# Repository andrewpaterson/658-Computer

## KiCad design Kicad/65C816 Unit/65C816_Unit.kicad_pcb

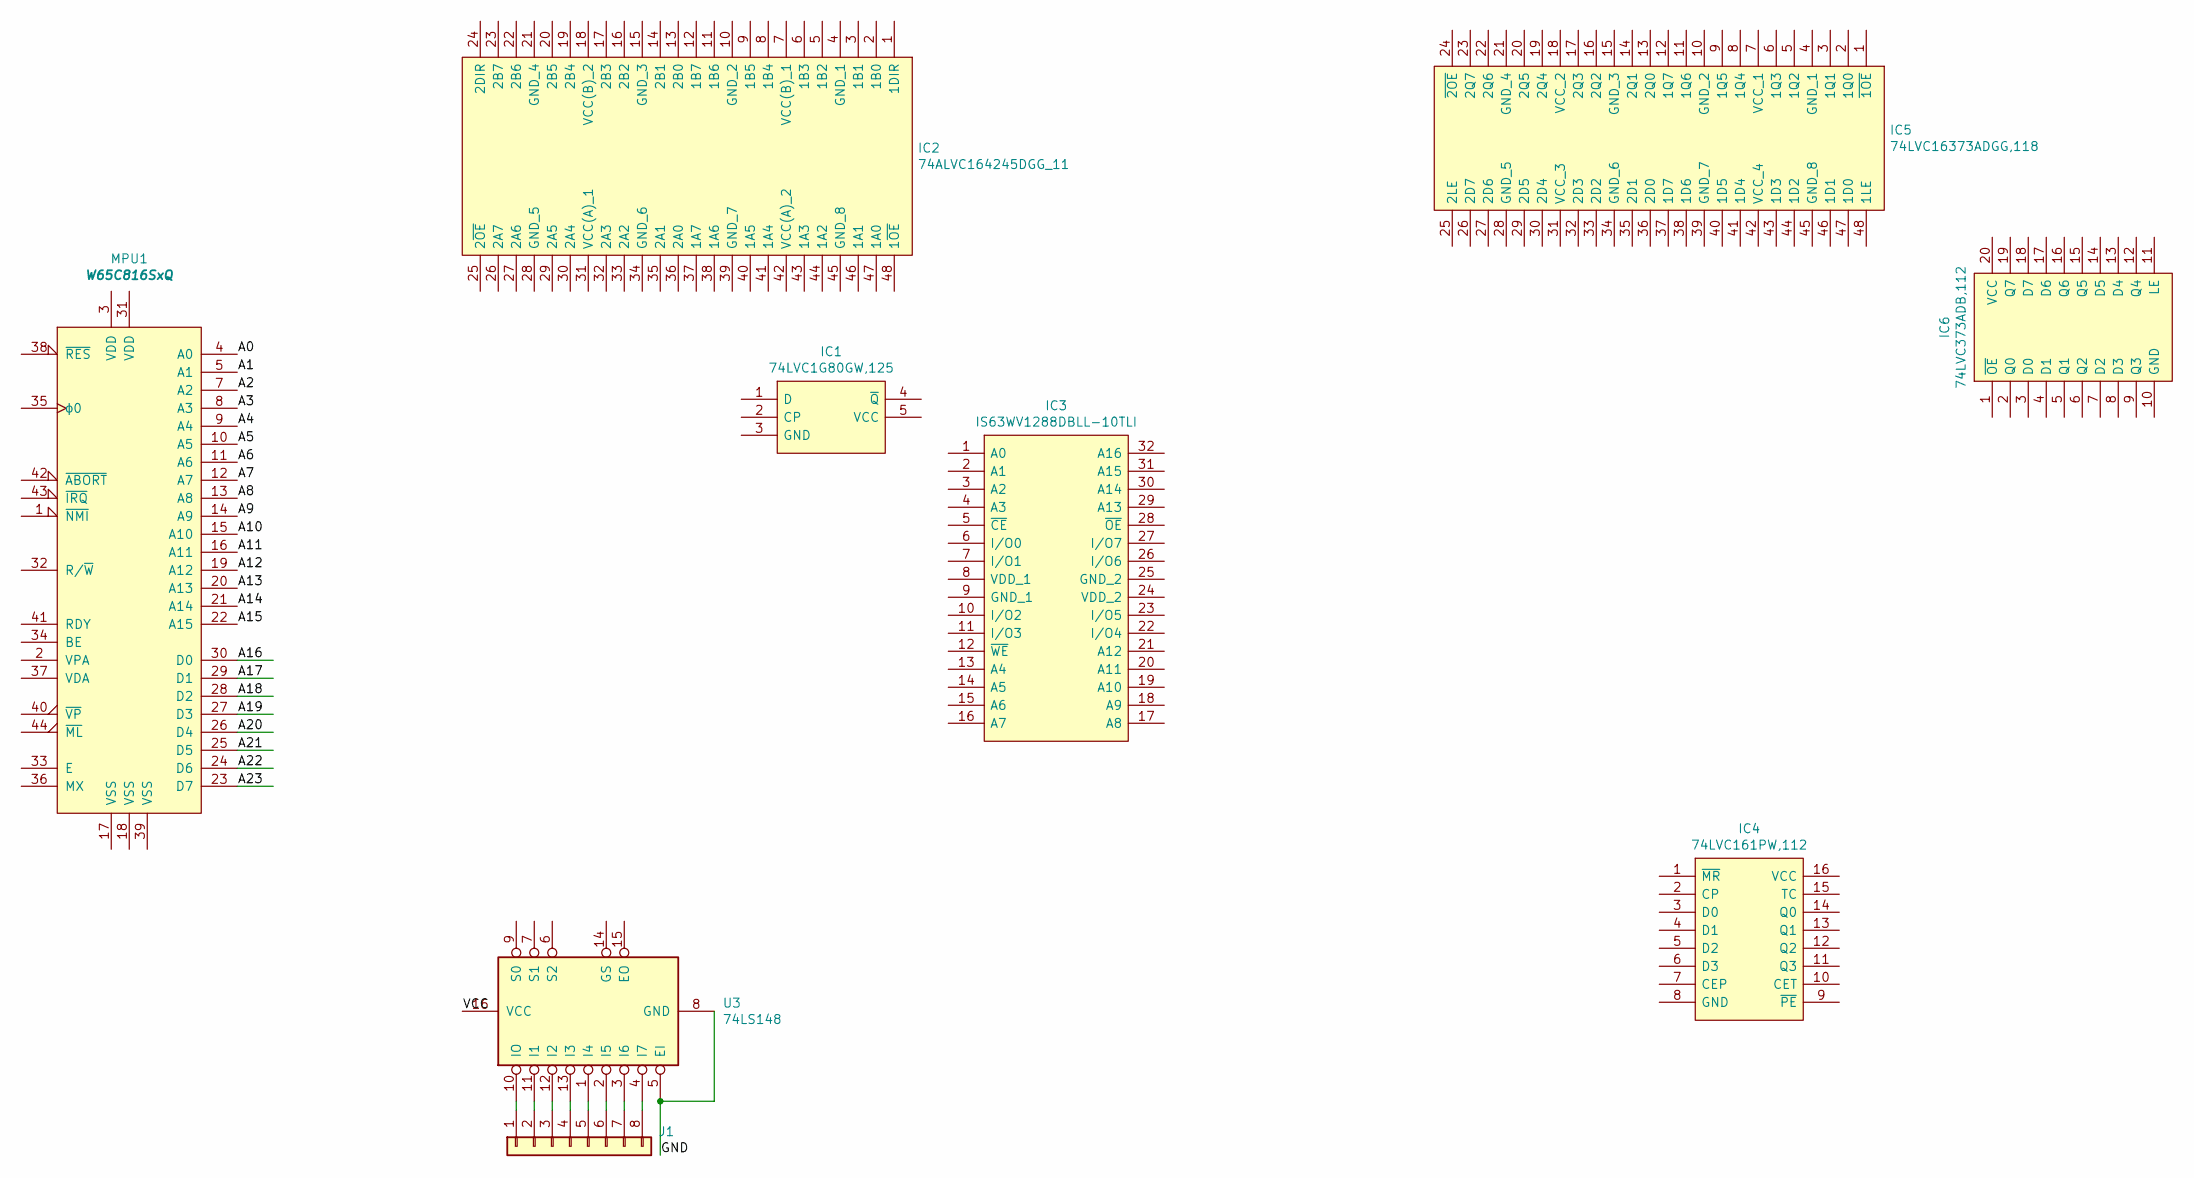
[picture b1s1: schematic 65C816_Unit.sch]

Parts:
IC1: 74LVC1G80GW,125; SOT65P212X110-5N; Mouser Part Number 771-LVC1G80GW125
IC2: 74ALVC164245DGG_11; SOP50P810X120-48N; Mouser Part Number 771-74ALVC164245
IC3: IS63WV1288DBLL-10TLI; SOIC127P1176X120-32N; Mouser Part Number 870-63WV1288DB10TLI
IC4: 74LVC161PW,112; SOP65P640X110-16N; Mouser Part Number 771-LVC161PW112
IC5: 74LVC16373ADGG,118; SOP50P810X120-48N; Mouser Part Number 771-74LVC16373ADGG1
IC6: 74LVC373ADB,112; SOP65P775X200-20N; Manufacturer_Part_Number 74LVC373ADB,112
J1: Conn_01x08; PinHeader_1x08_P2.54mm_Vertical
MPU1: W65C816SxQ; PQFP-44_10x10mm_P0.8mm
U3: 74LS148; SOIC-16_4.55x10.3mm_P1.27mm

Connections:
/A0: MPU1.4 (A0)
/A1: MPU1.5 (A1)
/A2: MPU1.7 (A2)
/A3: MPU1.8 (A3)
/A4: MPU1.9 (A4)
/A5: MPU1.10 (A5)
/A6: MPU1.11 (A6)
/A7: MPU1.12 (A7)
/A8: MPU1.13 (A8)
/A9: MPU1.14 (A9)
/A10: MPU1.15 (A10)
/A11: MPU1.16 (A11)
/A12: MPU1.19 (A12)
/A13: MPU1.20 (A13)
/A14: MPU1.21 (A14)
/A15: MPU1.22 (A15)
/A16: MPU1.30 (D0)
/A17: MPU1.29 (D1)
/A18: MPU1.28 (D2)
/A19: MPU1.27 (D3)
/A20: MPU1.26 (D4)
/A21: MPU1.25 (D5)
/A22: MPU1.24 (D6)
/A23: MPU1.23 (D7)
/GND: U3.5 (EI), U3.8 (GND)
/VCC: U3.16 (VCC)
unnamed: J1.1, U3.10 (IO)
unnamed: J1.2, U3.11 (I1)
unnamed: J1.3, U3.12 (I2)
unnamed: J1.4, U3.13 (I3)
unnamed: J1.5, U3.1 (I4)
unnamed: J1.6, U3.2 (I5)
unnamed: J1.7, U3.3 (I6)
unnamed: J1.8, U3.4 (I7)

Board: 2 copper layers, 9 parts (0 on the bottom side), 9 nets, no tracks yet.

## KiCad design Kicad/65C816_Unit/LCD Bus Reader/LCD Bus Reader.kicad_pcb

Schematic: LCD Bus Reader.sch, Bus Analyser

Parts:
C1, C2, C3: C; C_Disc_D3.8mm_W2.6mm_P2.50mm
D1, D2: D_Zener; D_A-405_P7.62mm_Horizontal
D3, D4, D5, D6: LED; LED_D5.0mm
D7, D8, D9, D10, D11, D12, D13, D14, D15, D16, D17, D18, D19, D20, D21, D22, D23, D24, D25, D26, D27, D28, D29, D30, D31, D32, D33, D34, D35, D36, D37, D38, D39, D40, D41, D42, D43, D44, D45, D46: 1N4148; D_T-1_P5.08mm_Horizontal
J1: Conn_01x02_Male; PinHeader_1x02_P2.54mm_Vertical
J2: Conn_01x24_Male; PinHeader_1x24_P2.54mm_Vertical
J3: Conn_01x03_Male; PinHeader_1x03_P2.54mm_Vertical
J4, J5: Conn_01x08_Male; PinHeader_1x08_P2.54mm_Vertical
R1, R2, R3, R4, R5, R6, R7, R8, R9, R10, R11, R12, R13, R14, R15, R16, R17, R18, R19, R20, R21, R22, R23, R24, R25, R26, R27, R28, R29, R30, R31, R32, R33, R34, R35, R36, R37, R38, R39, R40, R41, R42, R43, R44, R45: R; R_Axial_DIN0204_L3.6mm_D1.6mm_P5.08mm_Horizontal
RV1: R_POT; Potentiometer_Omeg_PC16BU_Vertical
U1: Pico; RPi_Pico_SMD_TH
U2: RC1602A; NMTC-S16205
U3: L7805; TO-220-3_Vertical
U4, U6, U7, U8, U9: 74LS373; SO-20_12.8x7.5mm_P1.27mm
U5: 74LS138; SO-16_3.9x9.9mm_P1.27mm

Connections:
+12V: J1.1, U3.1 (IN)
/0V: D2.1 (K), D3.1 (K), J1.2, RV1.1, U3.2 (GND)
/1.6V: C1.2, C2.2, C3.2, D1.2 (A), D4.1 (K), D5.1 (K), D6.1 (K), R1.2, U1.3 (GND), U1.23 (GND), U1.28 (GND), U1.33 (GND), U1.38 (GND), U2.1 (VSS), U4.10 (GND), U5.8 (GND), U6.10 (GND), U7.10 (GND), U8.10 (GND), U9.10 (GND)
/5V: C1.1, C2.1, C3.1, R1.1, R2.1, RV1.3, U1.39 (VSYS), U2.2 (VDD), U3.3 (OUT), U4.20 (VCC), U5.16 (VCC), U6.20 (VCC), U7.20 (VCC), U8.20 (VCC), U9.20 (VCC)
/CE0: U5.15 (O0), U6.1 (OE)
/CE1: U4.1 (OE), U5.14 (O1)
/CE2: U5.13 (O2), U7.1 (OE)
/CE3: U5.12 (O3), U8.1 (OE)
/CE4: U5.11 (O4), U9.1 (OE)
/CS0: U1.20 (GPIO15), U5.1 (A0)
/CS1: U1.32 (GPIO27_ADC1), U5.2 (A1)
/CS2: U1.34 (GPIO28_ADC2), U5.3 (A2)
/DB0: U1.14 (GPIO10), U2.7 (DB0)
/DB1: U1.12 (GPIO9), U2.8 (DB1)
/DB2: U1.11 (GPIO8), U2.9 (DB2)
/DB3: U1.10 (GPIO7), U2.10 (DB3)
/DB4: U1.9 (GPIO6), U2.11 (DB4)
/DB5: U1.7 (GPIO5), U2.12 (DB5)
/DB6: U1.6 (GPIO4), U2.13 (DB6)
/DB7: U1.5 (GPIO3), U2.14 (DB7)
/E: U1.15 (GPIO11), U2.6 (E)
/L0: U1.31 (GPIO26_ADC0), U4.2 (O0), U6.2 (O0), U7.2 (O0), U8.2 (O0), U9.2 (O0)
/L1: U1.29 (GPIO22), U4.5 (O1), U6.5 (O1), U7.5 (O1), U8.5 (O1), U9.5 (O1)
/L2: U1.27 (GPIO21), U4.6 (O2), U6.6 (O2), U7.6 (O2), U8.6 (O2), U9.6 (O2)
/L3: U1.26 (GPIO20), U4.9 (O3), U6.9 (O3), U7.9 (O3), U8.9 (O3), U9.9 (O3)
/L4: U1.25 (GPIO19), U4.12 (O4), U6.12 (O4), U7.12 (O4), U8.12 (O4), U9.12 (O4)
/L5: U1.24 (GPIO18), U4.15 (O5), U6.15 (O5), U7.15 (O5), U8.15 (O5), U9.15 (O5)
/L6: U1.22 (GPIO17), U4.16 (O6), U6.16 (O6), U7.16 (O6), U8.16 (O6), U9.16 (O6)
/L7: U1.21 (GPIO16), U4.19 (O7), U6.19 (O7), U7.19 (O7), U8.19 (O7), U9.19 (O7)
/LE: U1.19 (GPIO14), U4.11 (LE), U6.11 (LE), U7.11 (LE), U8.11 (LE), U9.11 (LE)
/P1: D7.2, U6.3 (D0)
/P2: D8.2, U6.4 (D1)
/P3: D9.2, U6.7 (D2)
/P4: D10.2, U6.8 (D3)
/P5: D11.2, U6.13 (D4)
/P6: D12.2, U6.14 (D5)
/P7: D13.2, U6.17 (D6)
/P8: D14.2, U6.18 (D7)
/P9: D15.2, U4.3 (D0)
/P10: D16.2, U4.4 (D1)
/P11: D17.2, U4.7 (D2)
/P12: D18.2, U4.8 (D3)
/P13: D19.2, U4.13 (D4)
/P14: D20.2, U4.14 (D5)
/P15: D21.2, U4.17 (D6)
/P16: D22.2, U4.18 (D7)
/P17: D23.2, U7.3 (D0)
/P18: D24.2, U7.4 (D1)
/P19: D25.2, U7.7 (D2)
/P20: D26.2, U7.8 (D3)
/P21: D27.2, U7.13 (D4)
/P22: D28.2, U7.14 (D5)
/P23: D29.2, U7.17 (D6)
/P24: D30.2, U7.18 (D7)
/P25: D31.2, U8.3 (D0)
/P26: D32.2, U8.4 (D1)
/P27: D33.2, U8.7 (D2)
/P28: D34.2, U8.8 (D3)
/P29: D35.2, U8.13 (D4)
/P30: D36.2, U8.14 (D5)
/P31: D37.2, U8.17 (D6)
/P32: D38.2, U8.18 (D7)
/P33: D39.2, U9.3 (D0)
/P34: D40.2, U9.4 (D1)
/P35: D41.2, U9.7 (D2)
/P36: D42.2, U9.8 (D3)
/P37: D43.2, U9.13 (D4)
/P38: D44.2, U9.14 (D5)
/P39: D45.2, U9.17 (D6)
/P40: D46.2, U9.18 (D7)
/RS: U1.17 (GPIO13), U2.4 (RS)
/RW: U1.16 (GPIO12), U2.5 (R/W)
/V0: RV1.2, U2.3 (VO)
unnamed: D1.1 (K), D2.2 (A)
unnamed: D3.2 (A), R2.2
unnamed: D4.2 (A), R43.1
unnamed: D5.2 (A), R44.1
unnamed: D6.2 (A), R45.2
unnamed: D7.1, R3.1
unnamed: D8.1, R4.1
unnamed: D9.1, R5.1
unnamed: D10.1, R6.1
unnamed: D11.1, R7.1
unnamed: D12.1, R8.1
unnamed: D13.1, R9.1
unnamed: D14.1, R10.1
unnamed: D15.1, R11.1
unnamed: D16.1, R12.1
unnamed: D17.1, R13.1
unnamed: D18.1, R14.1
unnamed: D19.1, R15.1
unnamed: D20.1, R16.1
unnamed: D21.1, R17.1
unnamed: D22.1, R18.1
unnamed: D23.1, R19.1
unnamed: D24.1, R20.1
unnamed: D25.1, R21.1
unnamed: D26.1, R22.1
unnamed: D27.1, R23.1
unnamed: D28.1, R24.1
unnamed: D29.1, R25.1
unnamed: D30.1, R26.1
unnamed: D31.1, R27.1
unnamed: D32.1, R28.1
unnamed: D33.1, R29.1
unnamed: D34.1, R30.1
unnamed: D35.1, R31.1
unnamed: D36.1, R32.1
unnamed: D37.1, R33.1
unnamed: D38.1, R34.1
unnamed: D39.1, R35.1
unnamed: D40.1, R36.1
unnamed: D41.1, R37.1
unnamed: D42.1, R38.1
unnamed: D43.1, R39.1
unnamed: D44.1, R40.1
unnamed: D45.1, R41.1
unnamed: D46.1, R42.1
unnamed: J2.1, R3.2
unnamed: J2.2, R4.2
unnamed: J2.3, R5.2
unnamed: J2.4, R6.2
unnamed: J2.5, R7.2
unnamed: J2.6, R8.2
unnamed: J2.7, R9.2
unnamed: J2.8, R10.2
unnamed: J2.9, R11.2
unnamed: J2.10, R12.2
unnamed: J2.11, R13.2
unnamed: J2.12, R14.2
unnamed: J2.13, R15.2
unnamed: J2.14, R16.2
unnamed: J2.15, R17.2
unnamed: J2.16, R18.2
unnamed: J2.17, R19.2
unnamed: J2.18, R20.2
unnamed: J2.19, R21.2
unnamed: J2.20, R22.2
unnamed: J2.21, R23.2
unnamed: J2.22, R24.2
unnamed: J2.23, R25.2
unnamed: J2.24, R26.2
unnamed: J3.1, U1.41 (SWCLK)
unnamed: J3.2, U1.42 (GND)
unnamed: J3.3, U1.43 (SWDIO)
unnamed: J4.1, R27.2
unnamed: J4.2, R28.2
unnamed: J4.3, R29.2
unnamed: J4.4, R30.2
unnamed: J4.5, R31.2
unnamed: J4.6, R32.2
unnamed: J4.7, R33.2
unnamed: J4.8, R34.2
unnamed: J5.1, R35.2
unnamed: J5.2, R36.2
unnamed: J5.3, R37.2
unnamed: J5.4, R38.2
unnamed: J5.5, R39.2
unnamed: J5.6, R40.2
unnamed: J5.7, R41.2
unnamed: J5.8, R42.2
unnamed: R43.2, U1.4 (GPIO2)
unnamed: R44.2, U1.2 (GPIO1)
unnamed: R45.1, U1.1 (GPIO0)

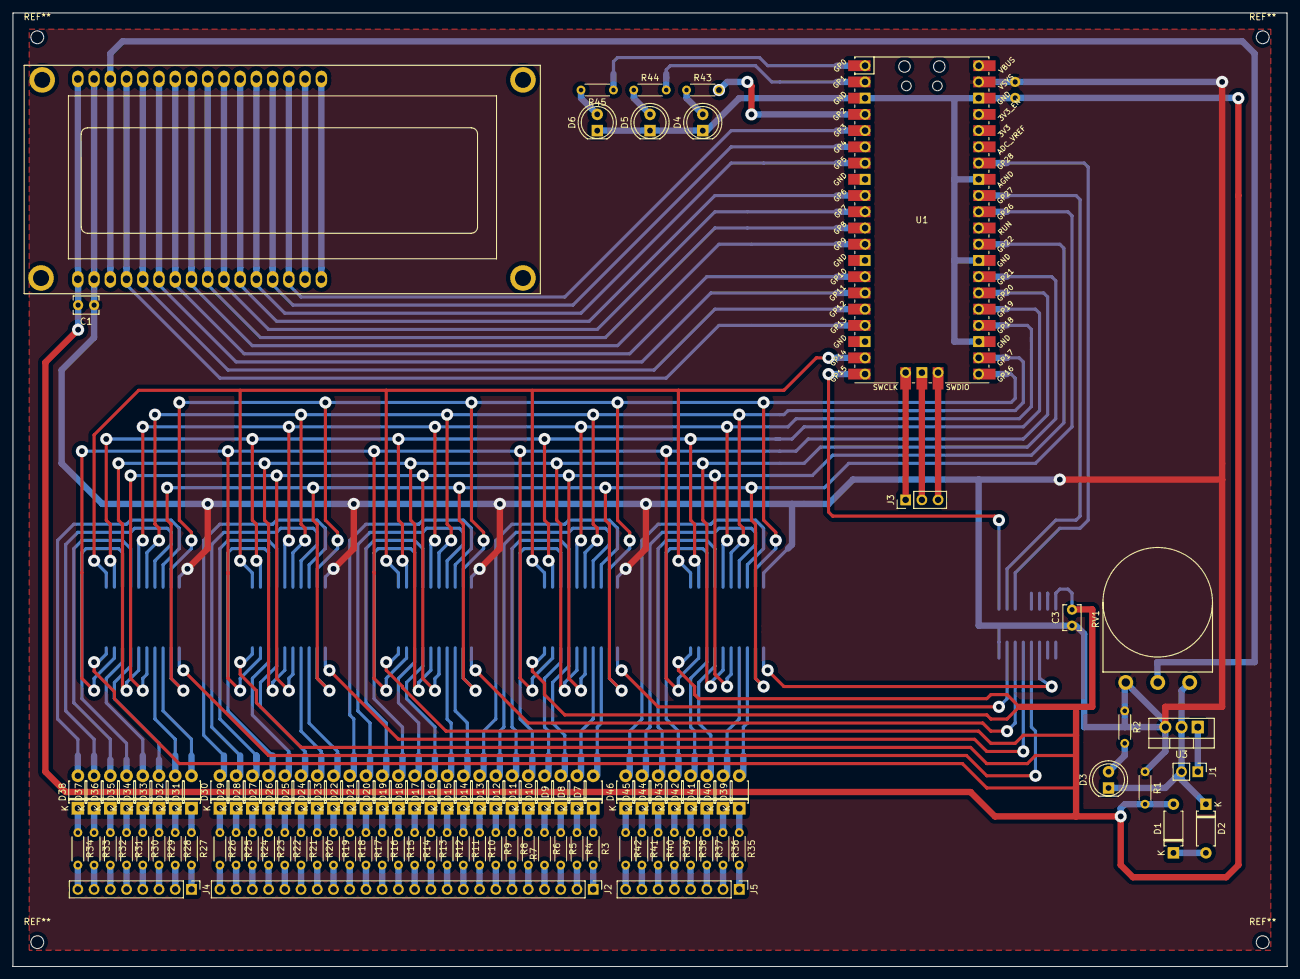
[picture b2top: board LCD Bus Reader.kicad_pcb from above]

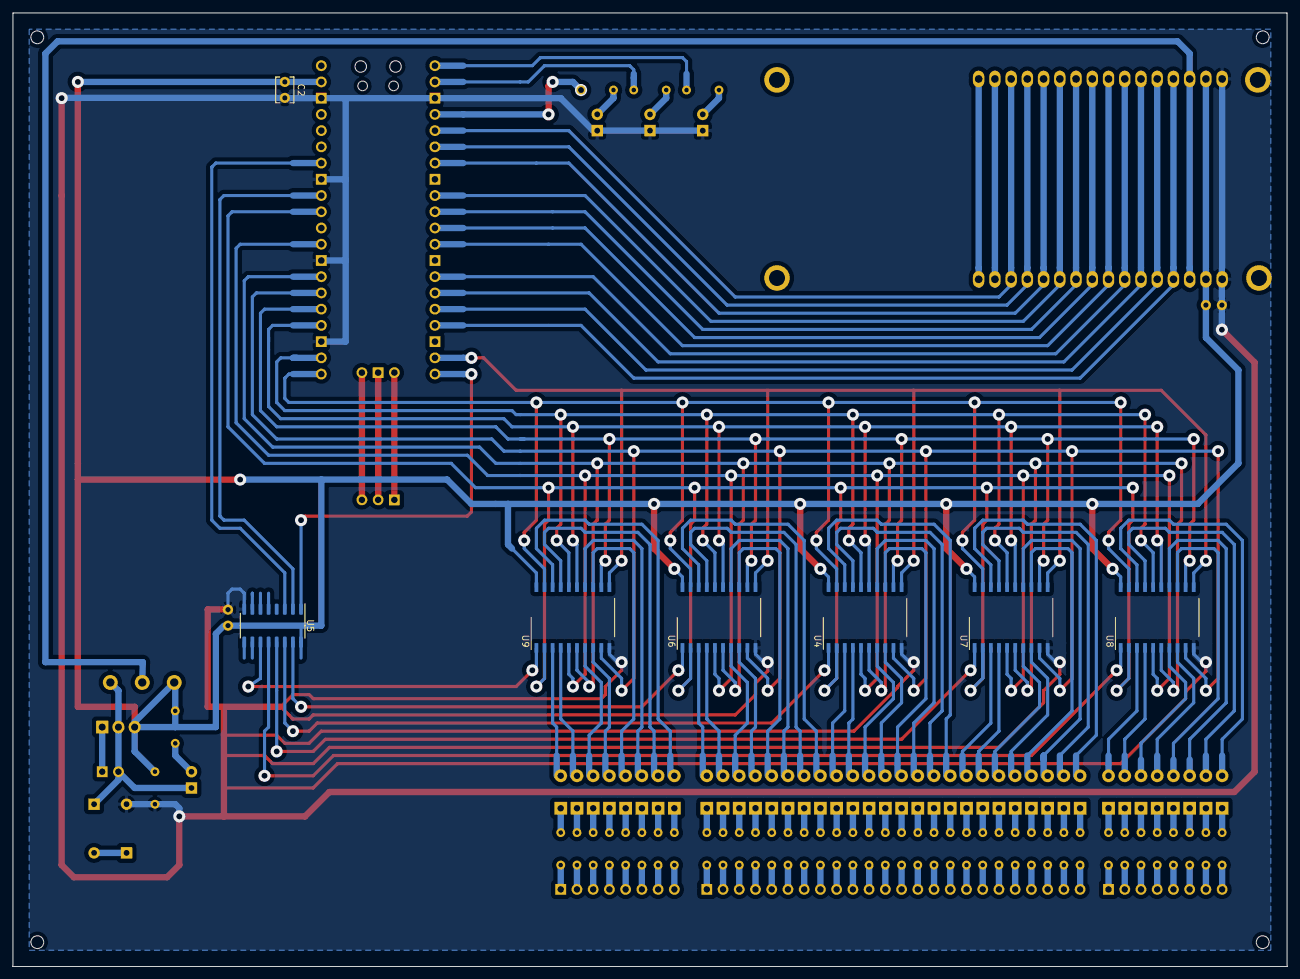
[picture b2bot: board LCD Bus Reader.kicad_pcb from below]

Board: 2 copper layers, 199.4 x 149.2 mm, 109 parts (7 on the bottom side), 164 nets.

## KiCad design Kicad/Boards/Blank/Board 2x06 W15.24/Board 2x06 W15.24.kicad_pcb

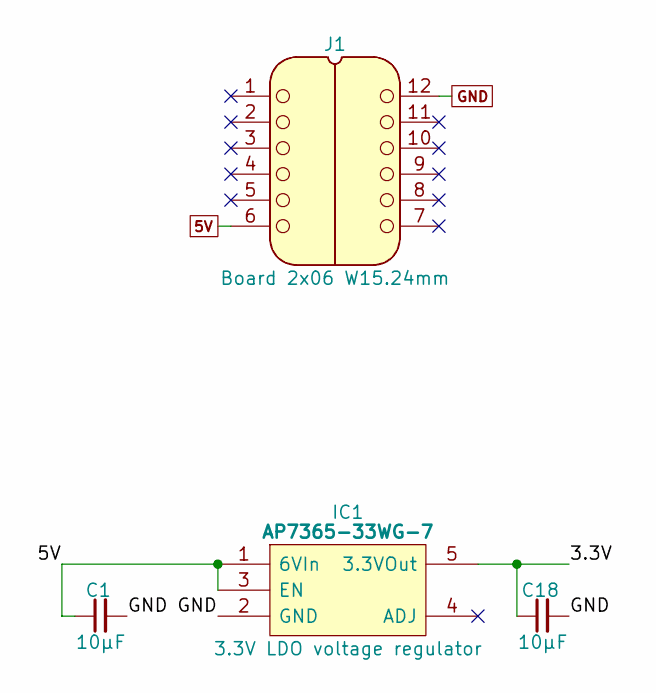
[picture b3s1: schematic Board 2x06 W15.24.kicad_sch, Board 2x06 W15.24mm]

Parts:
C1, C18: 10µF; C_0805
IC1: AP7365-33WG-7; SOT95P285X130-5N; Manufacturer_Part_Number AP7365-33WG-7; Mouser Part Number 621-AP7365-33WG-7
J1: Board 2x06 W15.24mm; DIP-12_Board_W15.24mm_Alt

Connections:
5V: C1.1, IC1.1 (6VIn), IC1.3 (EN), J1.6
/3.3V: C18.1, IC1.5 (3.3VOut)
GND: C1.2, C18.2, IC1.2 (GND), J1.12

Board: 2 copper layers, 4 parts (0 on the bottom side), 3 nets, no tracks yet.

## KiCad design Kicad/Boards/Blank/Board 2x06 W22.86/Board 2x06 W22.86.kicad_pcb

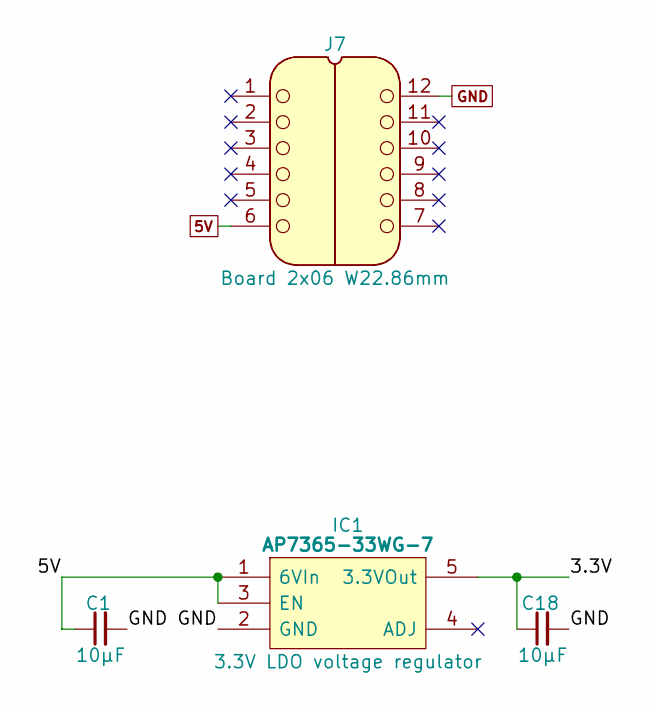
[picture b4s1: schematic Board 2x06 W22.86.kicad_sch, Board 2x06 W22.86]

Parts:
C1, C18: 10µF; C_0805
IC1: AP7365-33WG-7; SOT95P285X130-5N; Manufacturer_Part_Number AP7365-33WG-7; Mouser Part Number 621-AP7365-33WG-7
J7: Board 2x06 W22.86mm; DIP-12_Board_W22.86mm_Alt

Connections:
5V: C1.1, IC1.1 (6VIn), IC1.3 (EN), J7.6
/3.3V: C18.1, IC1.5 (3.3VOut)
GND: C1.2, C18.2, IC1.2 (GND), J7.12

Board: 2 copper layers, 4 parts (0 on the bottom side), 3 nets, no tracks yet.

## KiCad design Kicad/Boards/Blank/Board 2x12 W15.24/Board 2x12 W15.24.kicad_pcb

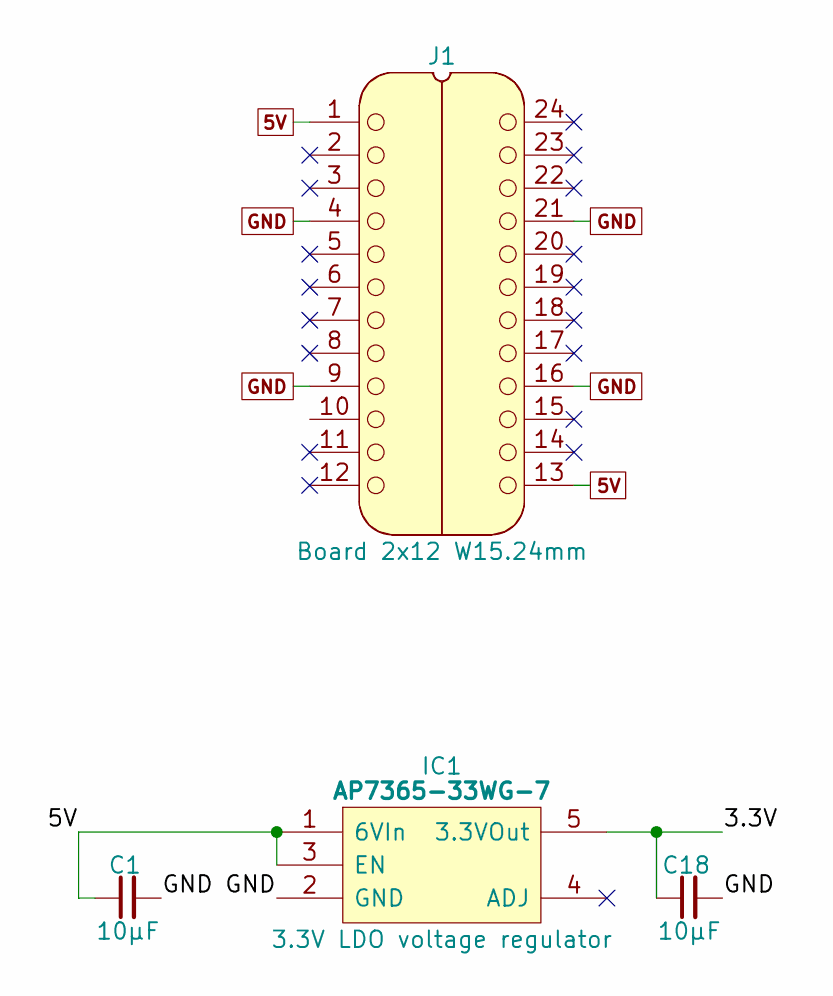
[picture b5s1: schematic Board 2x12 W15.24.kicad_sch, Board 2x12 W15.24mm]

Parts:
C1, C18: 10µF; C_0805
IC1: AP7365-33WG-7; SOT95P285X130-5N; Manufacturer_Part_Number AP7365-33WG-7; Mouser Part Number 621-AP7365-33WG-7
J1: Board 2x12 W15.24mm; DIP-24_Board_W15.24mm

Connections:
5V: C1.1, IC1.1 (6VIn), IC1.3 (EN), J1.1, J1.13
/3.3V: C18.1, IC1.5 (3.3VOut)
GND: C1.2, C18.2, IC1.2 (GND), J1.4, J1.9, J1.16, J1.21

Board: 2 copper layers, 4 parts (0 on the bottom side), 3 nets, no tracks yet.

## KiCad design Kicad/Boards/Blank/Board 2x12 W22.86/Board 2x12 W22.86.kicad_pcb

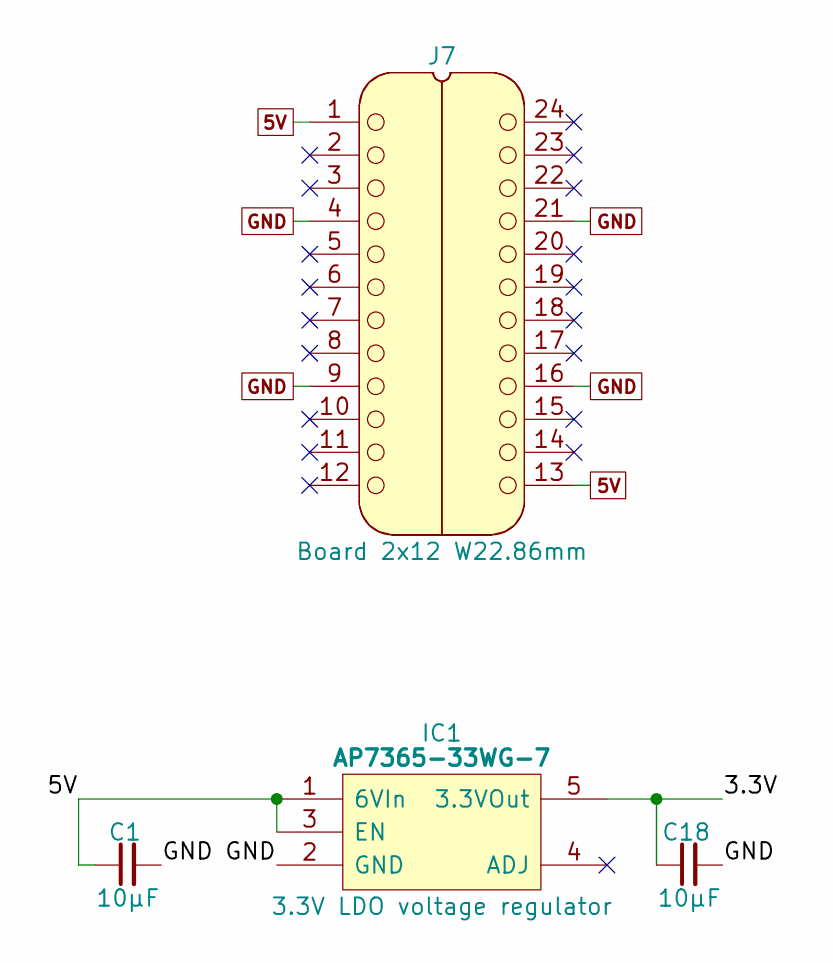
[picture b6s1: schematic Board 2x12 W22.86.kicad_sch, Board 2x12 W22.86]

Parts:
C1, C18: 10µF; C_0805
IC1: AP7365-33WG-7; SOT95P285X130-5N; Manufacturer_Part_Number AP7365-33WG-7; Mouser Part Number 621-AP7365-33WG-7
J7: Board 2x12 W22.86mm; DIP-24_Board_W22.86mm

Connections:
5V: C1.1, IC1.1 (6VIn), IC1.3 (EN), J7.1, J7.13
/3.3V: C18.1, IC1.5 (3.3VOut)
GND: C1.2, C18.2, IC1.2 (GND), J7.4, J7.9, J7.16, J7.21

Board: 2 copper layers, 4 parts (0 on the bottom side), 3 nets, no tracks yet.

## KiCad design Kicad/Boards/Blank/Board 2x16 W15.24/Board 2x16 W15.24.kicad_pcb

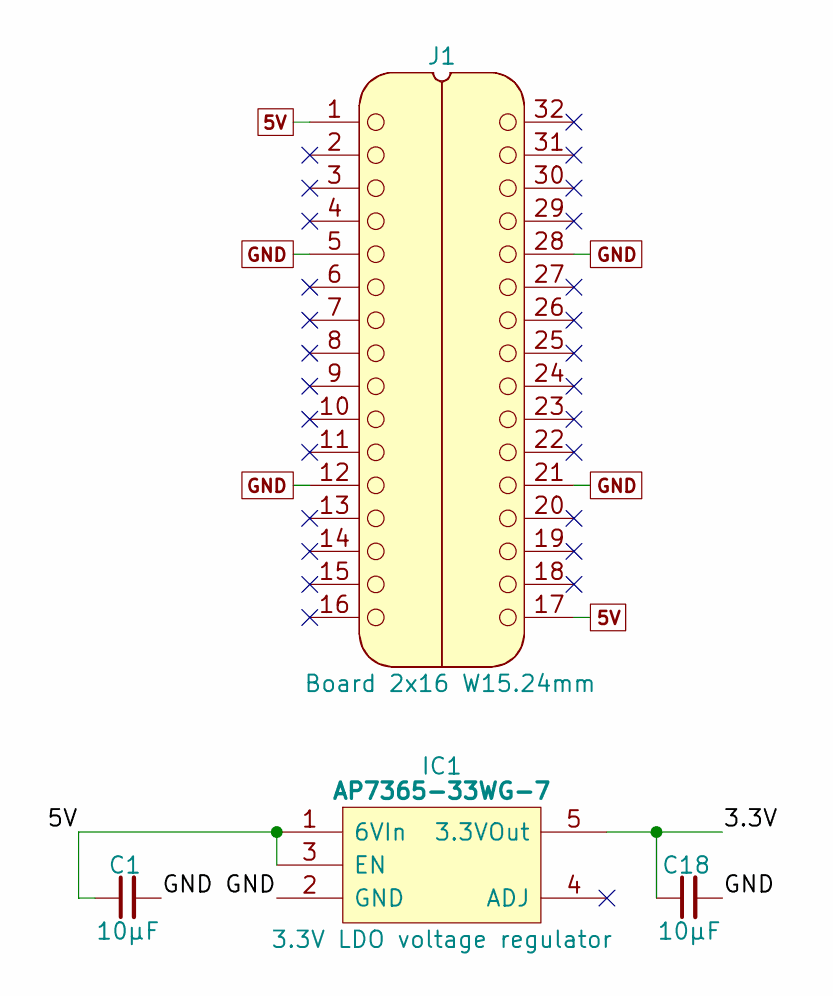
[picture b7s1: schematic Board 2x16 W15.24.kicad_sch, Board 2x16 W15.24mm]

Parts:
C1, C18: 10µF; C_0805
IC1: AP7365-33WG-7; SOT95P285X130-5N; Manufacturer_Part_Number AP7365-33WG-7; Mouser Part Number 621-AP7365-33WG-7
J1: Board 2x16 W15.24mm; DIP-32_Board_W15.24mm

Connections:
5V: C1.1, IC1.1 (6VIn), IC1.3 (EN), J1.1, J1.17
/3.3V: C18.1, IC1.5 (3.3VOut)
GND: C1.2, C18.2, IC1.2 (GND), J1.5, J1.12, J1.21, J1.28

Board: 2 copper layers, 4 parts (0 on the bottom side), 3 nets, no tracks yet.
